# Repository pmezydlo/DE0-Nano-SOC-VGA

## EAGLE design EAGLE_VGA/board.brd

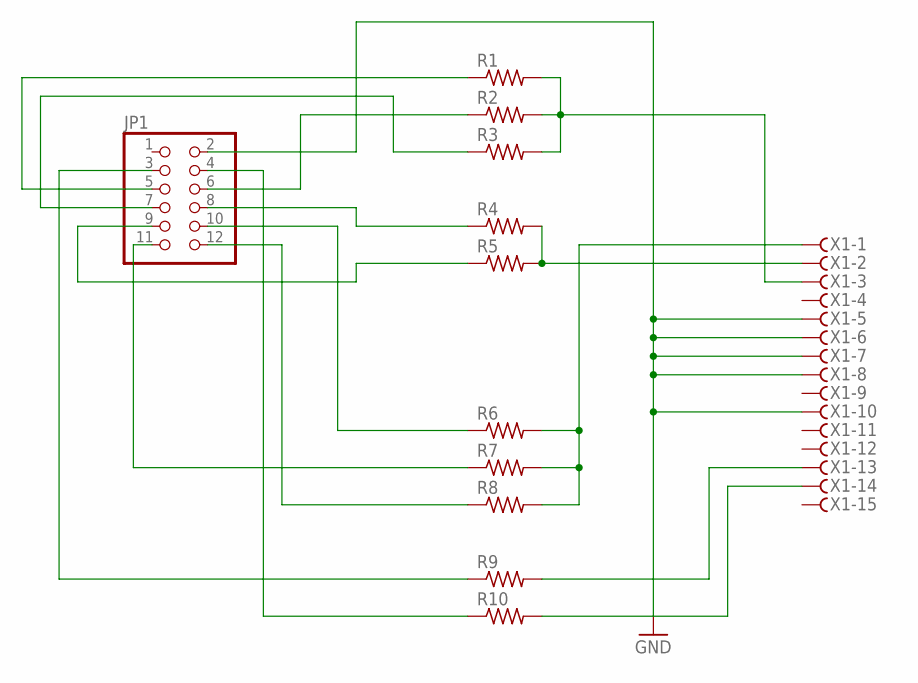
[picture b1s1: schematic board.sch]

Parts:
JP1: PINHD-2X6; 2X06
R1, R2, R3, R4, R5, R6, R7, R8, R9, R10: R-US_R0805; R0805
X1: F15HDHS; HDF15H

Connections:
GND: JP1.2, X1.5, X1.6, X1.7, X1.8, X1.10
unnamed: R1.2, R2.2, R3.2, X1.3
unnamed: R4.2, R5.2, X1.2
unnamed: R6.2, R7.2, R8.2, X1.1
unnamed: R9.2, X1.13
unnamed: R10.2, X1.14
unnamed: JP1.3, R9.1
unnamed: JP1.4, R10.1
unnamed: JP1.5, R1.1
unnamed: JP1.6, R2.1
unnamed: JP1.7, R3.1
unnamed: JP1.8, R4.1
unnamed: JP1.9, R5.1
unnamed: JP1.10, R6.1
unnamed: JP1.11, R7.1
unnamed: JP1.12, R8.1

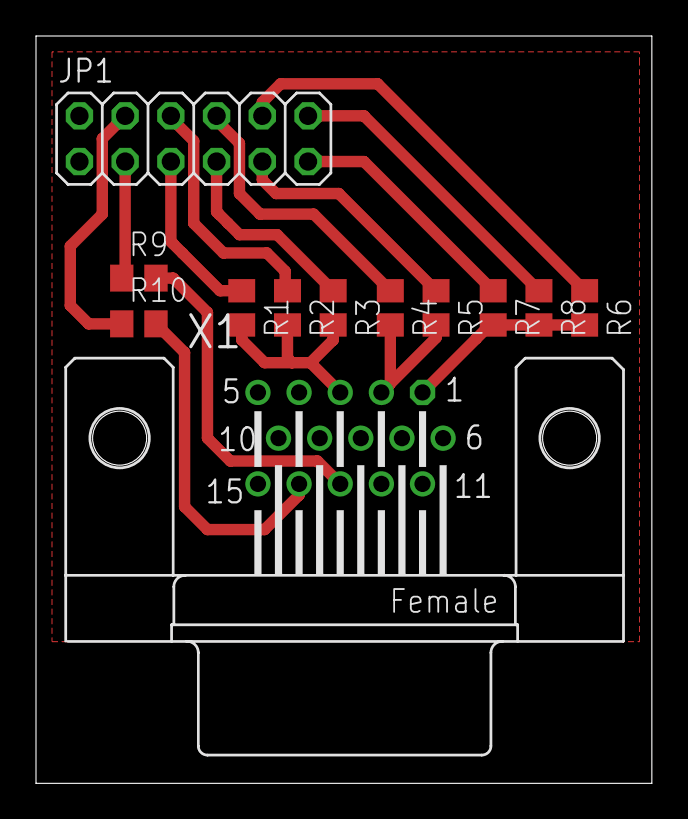
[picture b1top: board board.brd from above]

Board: 2 copper layers, 34.2 x 41.5 mm, 12 parts (0 on the bottom side), 16 nets.

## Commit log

2015-09-05 VGA
    VHDL code
2015-09-05 ref1
2015-09-09 VGA2
